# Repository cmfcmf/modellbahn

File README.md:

# Modellbahn

Eine Sammlung von Hardware und Software, die ich auf meiner Modelleisenbahnanlage verwende.

Eine Übersicht über alle Projekte ist hier zu finden: https://cmfcmf.github.io/modellbahn.

Lokal kann man die Website folgendermaßen bauen:

    bundle exec jekyll serve --livereload

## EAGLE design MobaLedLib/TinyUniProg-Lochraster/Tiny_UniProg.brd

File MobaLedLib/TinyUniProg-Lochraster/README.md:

---
layout: project
tags: [arduino, arduino nano, mobaledlib]
permalink: mobaledlib/tiny-uni-prog-lochraster-arduino-nano
state: finished
---

# Lochraster-Version der _TinyUniProg_-Platine für die MobaLedLib für Arduino Nano

Bei diesem Projekt handelt es sich um eine Lochraster-Variante der _TinyUniProg_-Platine der [MobaLedLib](https://github.com/Hardi-St/MobaLedLib_Docu).
Sie basiert auf dem [Original-Schaltplan](https://github.com/Hardi-St/MobaLedLib_Docu/blob/75f16147031ef20691729545cb87e0a1215a445a/Platinen/Tiny_UniProg.zip), allerdings ohne Debug-Hardware und auf Basis eines Arduino Nano statt Uno.

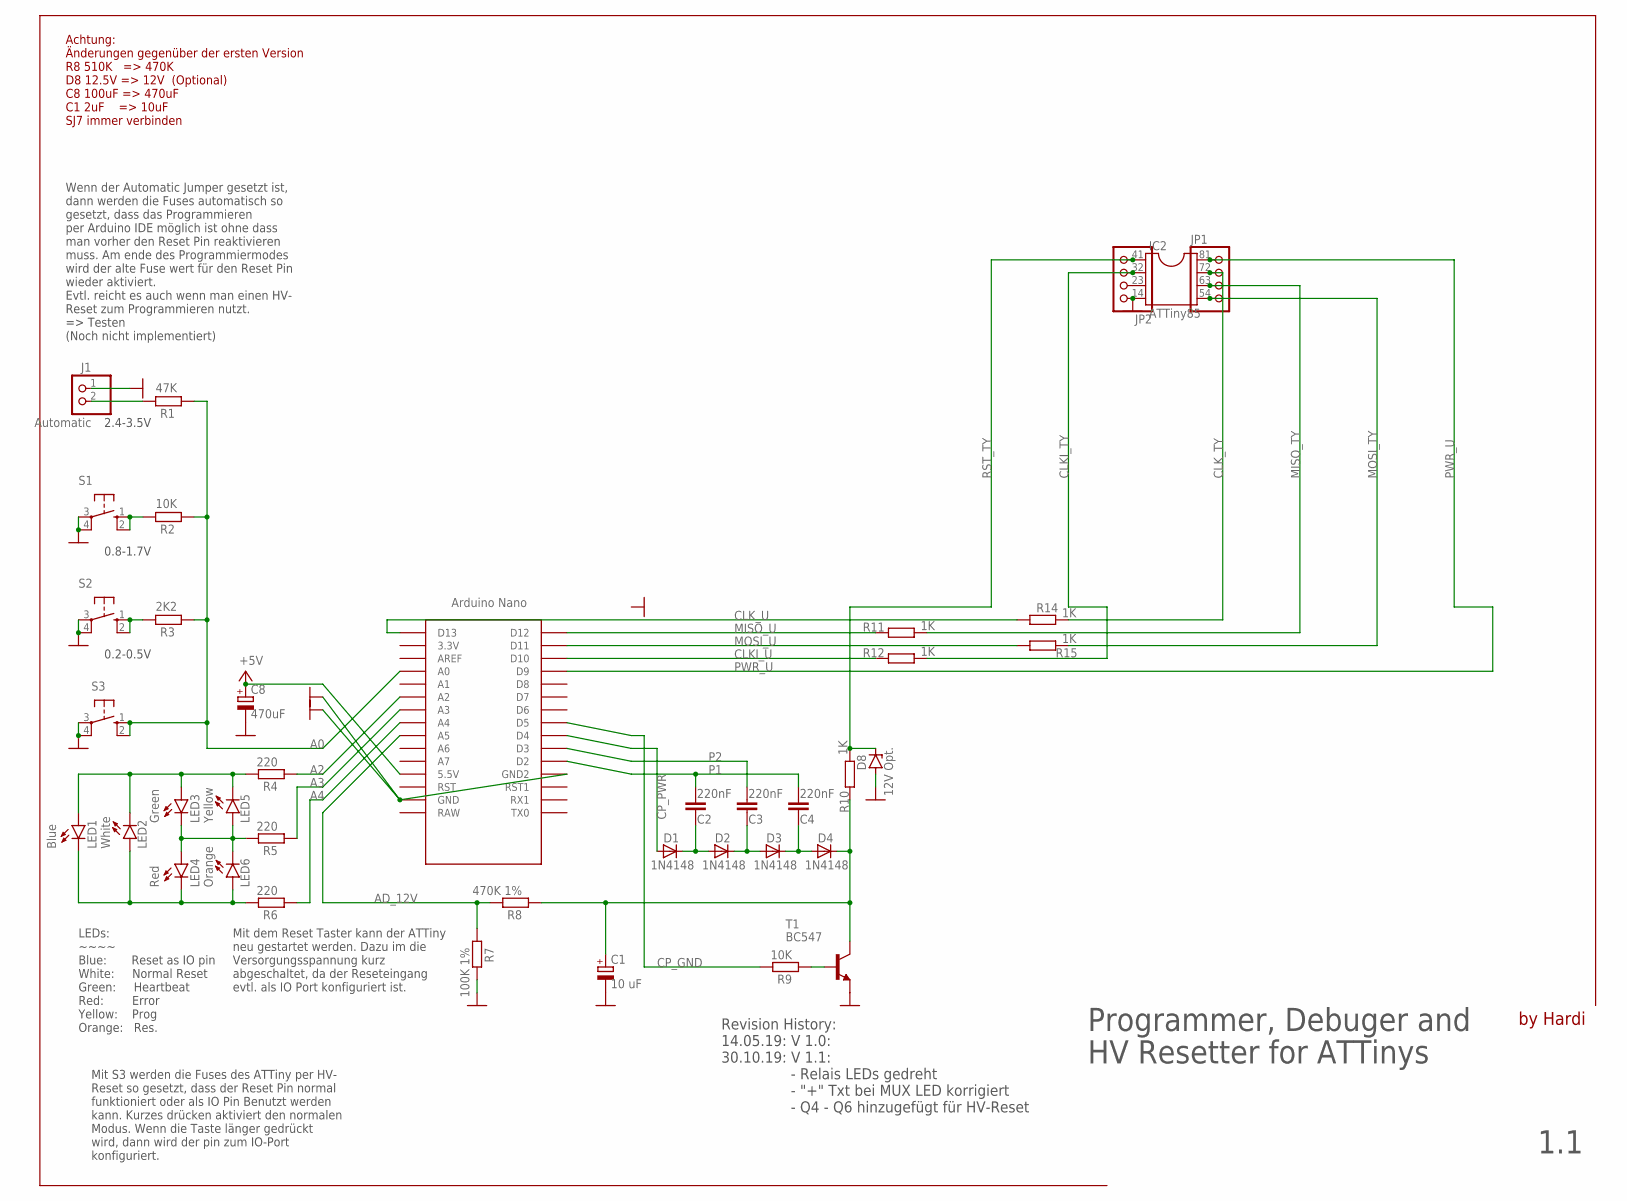
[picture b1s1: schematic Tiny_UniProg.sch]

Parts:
C1: 10 uF; E5-5
C2, C3, C4: 220nF; C050-024X044
C8: 470uF; E5-10,5
D1, D2, D3, D4: 1N4148; DO35-2
D8: 12V Opt.; ZDIO-2.5
IC2: ATTiny85; DIL08
J1: Automatic; 1X02
JP1, JP2: PINHD-1X4; 1X04
LED1: Blue; LED3MM
LED2: White; LED3MM
LED3: Green; LED3MM
LED4: Red; LED3MM
LED5: Yellow; LED3MM
LED6: Orange; LED3MM
R1: 47K; 0204V
R2: 10K; 0204V
R3: 2K2; 0204V
R4, R6: 220; 0204/5
R5: 220; 0204V
R7: 100K 1%; 0204/7
R8: 470K 1%; 0204V
R9: 10K; 0207/12
R10, R11: 1K; 0204V
R12, R15: 1K; 0204/5
R14: 1K; 0207/12
S1, S2, S3: 10-XX; B3F-10XX
T1: BC547; TO92
U$1: NANO

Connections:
+5V: C8.+, U$1.5V (5.5V)
A0: R1.1, R2.1, R3.1, S3.1 (S), S3.2 (S1), U$1.A0
A2: R4.1, U$1.A2
A3: R5.1, U$1.A3
A4: R6.1, U$1.A4
AD_12V: R7.1, R8.2, U$1.A5
CLKI_TY: IC2.2, JP2.3, R12.2
CLKI_U: R12.1, U$1.D10
CLK_TY: IC2.7, JP1.2, R14.2
CLK_U: R14.1, U$1.D13
CP_GND: R9.2, U$1.D5
CP_PWR: D1.A, U$1.D4
GND: C1.-, C8.-, D8.A, IC2.4, J1.1, JP2.1, R7.2, S1.3, S1.4 (P1), S2.3, S2.4 (P1), S3.3, S3.4 (P1), T1.1 (E), U$1.GND, U$1.GND1 (GND2)
MISO_TY: IC2.6, JP1.3, R11.2
MISO_U: R11.1, U$1.D12
MOSI_TY: IC2.5, JP1.4, R15.2
MOSI_U: R15.1, U$1.D11
unnamed: C2.2, D1.C, D2.A
unnamed: C3.2, D2.C, D3.A
unnamed: C4.2, D3.C, D4.A
unnamed: IC2.3, JP2.2
unnamed: R9.1, T1.2 (B)
unnamed: C1.+, D4.C, R8.1, R10.2, T1.3 (C)
unnamed: J1.2, R1.2
unnamed: R3.2, S2.1 (S), S2.2 (S1)
unnamed: LED1.A, LED2.K (C), LED3.A, LED5.K (C), R4.2
unnamed: LED3.K (C), LED4.A, LED5.A, LED6.K (C), R5.2
unnamed: LED1.K (C), LED2.A, LED4.K (C), LED6.A, R6.2
unnamed: R2.2, S1.1 (S), S1.2 (S1)
P1: C2.1, C4.1, U$1.D2
P2: C3.1, U$1.D3
PWR_U: IC2.8, JP1.1, U$1.D9
RST_TY: D8.C, IC2.1, JP2.4, R10.1

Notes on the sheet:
Mit S3 werden die Fuses des ATTiny per HV- Reset so gesetzt, dass der Reset Pin normal funktioniert oder als IO Pin Benutzt werden kann. Kurzes drücken aktiviert den normalen Modus. Wenn die Taste länger gedrückt wird, dann wird der pin zum IO-Port konfiguriert.
Mit dem Reset Taster kann der ATTiny neu gestartet werden. Dazu im die Versorgungsspannung kurz abgeschaltet, da der Reseteingang evtl. als IO Port konfiguriert ist.
Wenn der Automatic Jumper gesetzt ist, dann werden die Fuses automatisch so gesetzt, dass das Programmieren per Arduino IDE möglich ist ohne dass man vorher den Reset Pin reaktivieren muss. Am ende des Programmiermodes wird der alte Fuse wert für den Reset Pin wieder aktiviert. Evtl. reicht es auch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
LEDs: ~~~~ Blue: Reset as IO pin White: Normal Reset Green: Heartbeat Red: Error Yellow: Prog Orange: Res.
by Hardi
Programmer, Debuger and HV Resetter for ATTinys
0.2-0.5V
0.8-1.7V
2.4-3.5V
Achtung: Änderungen gegenüber der ersten Version R8 510K => 470K D8 12.5V => 12V (Optional) C8 100uF => 470uF C1 2uF => 10uF SJ7 immer verbinden
Revision History: 14.05.19: V 1.0: 30.10.19: V 1.1: - Relais LEDs gedreht - "+" Txt bei MUX LED korrigiert - Q4 - Q6 hinzugefügt für HV-Reset
1.1

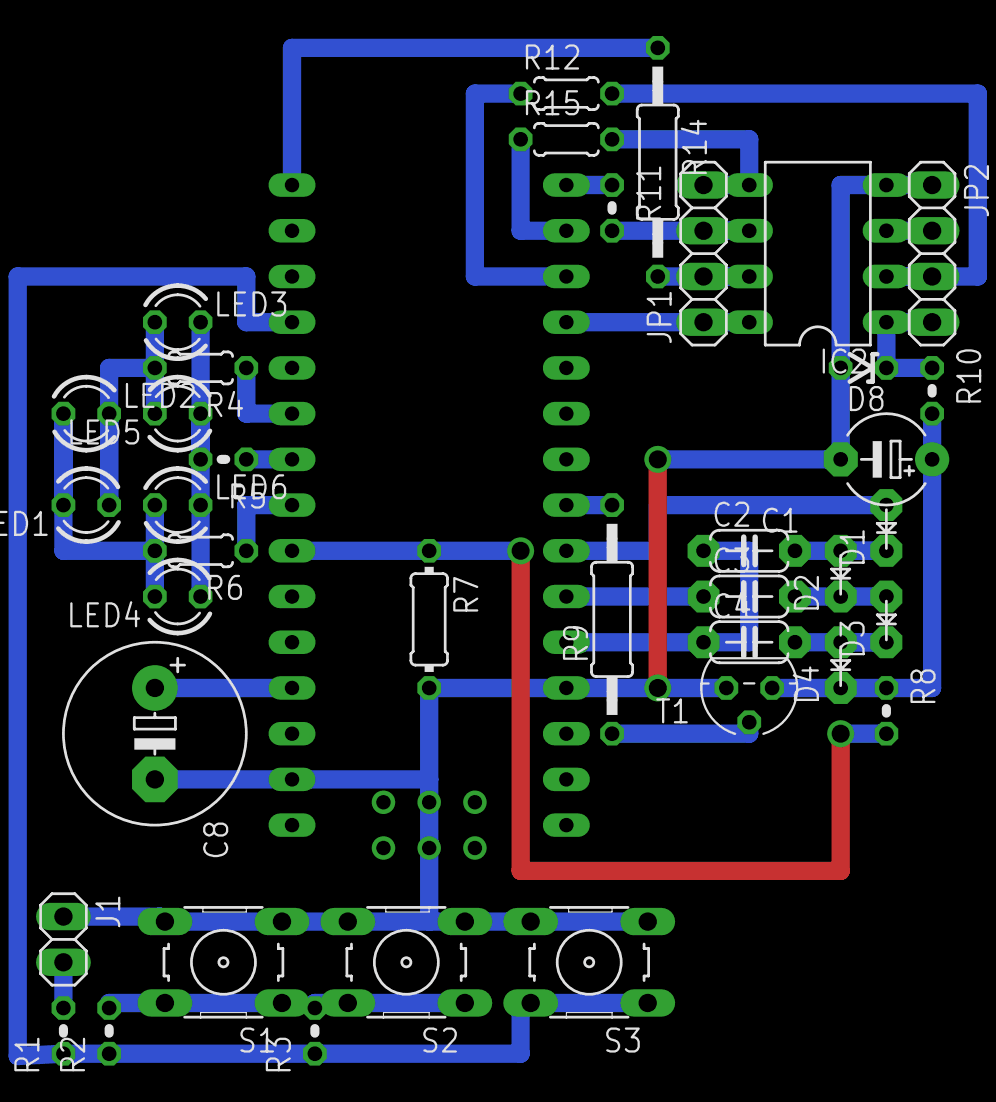
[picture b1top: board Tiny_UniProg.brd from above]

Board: 2 copper layers, 39 parts (0 on the bottom side), 33 nets.

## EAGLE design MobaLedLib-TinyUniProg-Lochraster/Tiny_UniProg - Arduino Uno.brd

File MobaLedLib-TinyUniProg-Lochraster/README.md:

---
layout: project
tags: [arduino, arduino nano, mobaledlib]
permalink: mobaledlib/tiny-uni-prog-lochraster-arduino-nano
state: finished
---

# Lochraster-Version der _TinyUniProg_-Platine für die MobaLedLib für Arduino Nano

Bei diesem Projekt handelt es sich um eine Lochraster-Variante der _TinyUniProg_-Platine der [MobaLedLib](https://github.com/Hardi-St/MobaLedLib_Docu).
Sie basiert auf dem [Original-Schaltplan](https://github.com/Hardi-St/MobaLedLib_Docu/blob/75f16147031ef20691729545cb87e0a1215a445a/Platinen/Tiny_UniProg.zip), allerdings ohne Debug-Hardware und auf Basis eines Arduino Nano statt Uno.

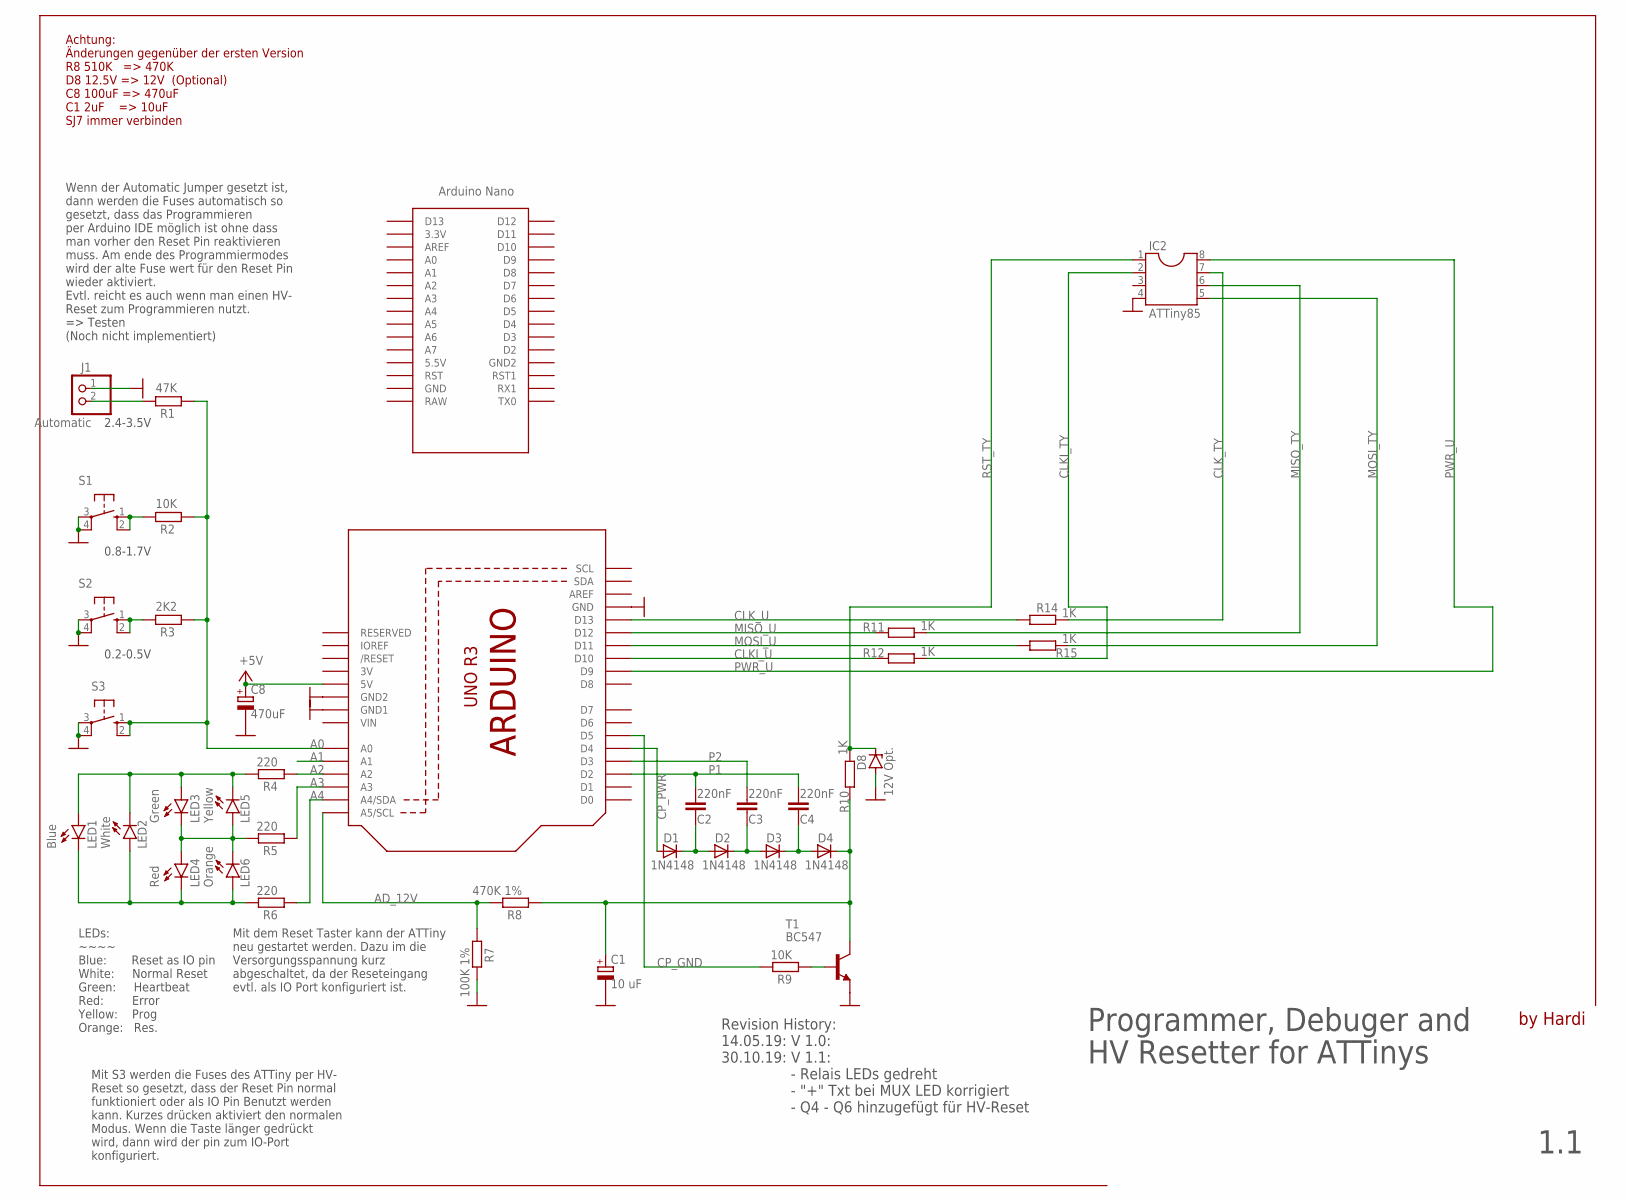
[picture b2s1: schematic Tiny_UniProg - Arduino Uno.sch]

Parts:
C1: 10 uF; E5-5
C2, C3, C4: 220nF; C050-024X044
C8: 470uF; E5-10,5
D1, D2, D3, D4: 1N4148; DO35-2
D8: 12V Opt.; ZDIO-2.5
IC2: ATTiny85; DIL08
J1: Automatic; 1X02
LED1: Blue; LED3MM
LED2: White; LED3MM
LED3: Green; LED3MM
LED4: Red; LED3MM
LED5: Yellow; LED3MM
LED6: Orange; LED3MM
R1: 47K; 0204/5
R2: 10K; 0204V
R3: 2K2; 0204V
R4, R6: 220; 0204/5
R5: 220; 0204V
R7: 100K 1%; 0204/7
R8: 470K 1%; 0204V
R9: 10K; 0204/7
R10: 1K; 0207/15
R11, R14, R15: 1K; 0204V
R12: 1K; 0207/7
S1, S2, S3: 10-XX; B3F-10XX
T1: BC547; TO92
U1: ARDUINOR3-DIMENSION; ARDUINOR3
U$1: NANO

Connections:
3V: U1.3V
+5V: C8.+, U1.5V
A0: R1.1, R2.1, R3.1, S3.1 (S), S3.2 (S1), U1.A0
A1: U1.A1
A2: R4.1, U1.A2
A3: R5.1, U1.A3
A4: R6.1, U1.A4 (A4/SDA)
AD_12V: R7.1, R8.2, U1.A5 (A5/SCL)
CLKI_TY: IC2.2, R12.2
CLKI_U: R12.1, U1.D10
CLK_TY: IC2.7, R14.2
CLK_U: R14.1, U1.D13
CP_GND: R9.2, U1.D5
CP_PWR: D1.A, U1.D4
GND: C1.-, C8.-, D8.A, IC2.4, J1.1, R7.2, S1.3, S1.4 (P1), S2.3, S2.4 (P1), S3.3, S3.4 (P1), T1.1 (E), U1.GND, U1.GND1, U1.GND2
MISO_TY: IC2.6, R11.2
MISO_U: R11.1, U1.D12
MOSI_TY: IC2.5, R15.2
MOSI_U: R15.1, U1.D11
unnamed: C2.2, D1.C, D2.A
unnamed: C3.2, D2.C, D3.A
unnamed: C4.2, D3.C, D4.A
unnamed: R9.1, T1.2 (B)
unnamed: C1.+, D4.C, R8.1, R10.2, T1.3 (C)
unnamed: J1.2, R1.2
unnamed: R3.2, S2.1 (S), S2.2 (S1)
unnamed: LED1.A, LED2.K (C), LED3.A, LED5.K (C), R4.2
unnamed: LED3.K (C), LED4.A, LED5.A, LED6.K (C), R5.2
unnamed: LED1.K (C), LED2.A, LED4.K (C), LED6.A, R6.2
unnamed: R2.2, S1.1 (S), S1.2 (S1)
P1: C2.1, C4.1, U1.D2
P2: C3.1, U1.D3
PWR_U: IC2.8, U1.D9
RST_TY: D8.C, IC2.1, R10.1
VIN: U1.VIN

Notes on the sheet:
Mit S3 werden die Fuses des ATTiny per HV- Reset so gesetzt, dass der Reset Pin normal funktioniert oder als IO Pin Benutzt werden kann. Kurzes drücken aktiviert den normalen Modus. Wenn die Taste länger gedrückt wird, dann wird der pin zum IO-Port konfiguriert.
Mit dem Reset Taster kann der ATTiny neu gestartet werden. Dazu im die Versorgungsspannung kurz abgeschaltet, da der Reseteingang evtl. als IO Port konfiguriert ist.
Wenn der Automatic Jumper gesetzt ist, dann werden die Fuses automatisch so gesetzt, dass das Programmieren per Arduino IDE möglich ist ohne dass man vorher den Reset Pin reaktivieren muss. Am ende des Programmiermodes wird der alte Fuse wert für den Reset Pin wieder aktiviert. Evtl. reicht es auch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
LEDs: ~~~~ Blue: Reset as IO pin White: Normal Reset Green: Heartbeat Red: Error Yellow: Prog Orange: Res.
by Hardi
Programmer, Debuger and HV Resetter for ATTinys
0.2-0.5V
0.8-1.7V
2.4-3.5V
Achtung: Änderungen gegenüber der ersten Version R8 510K => 470K D8 12.5V => 12V (Optional) C8 100uF => 470uF C1 2uF => 10uF SJ7 immer verbinden
Revision History: 14.05.19: V 1.0: 30.10.19: V 1.1: - Relais LEDs gedreht - "+" Txt bei MUX LED korrigiert - Q4 - Q6 hinzugefügt für HV-Reset
1.1

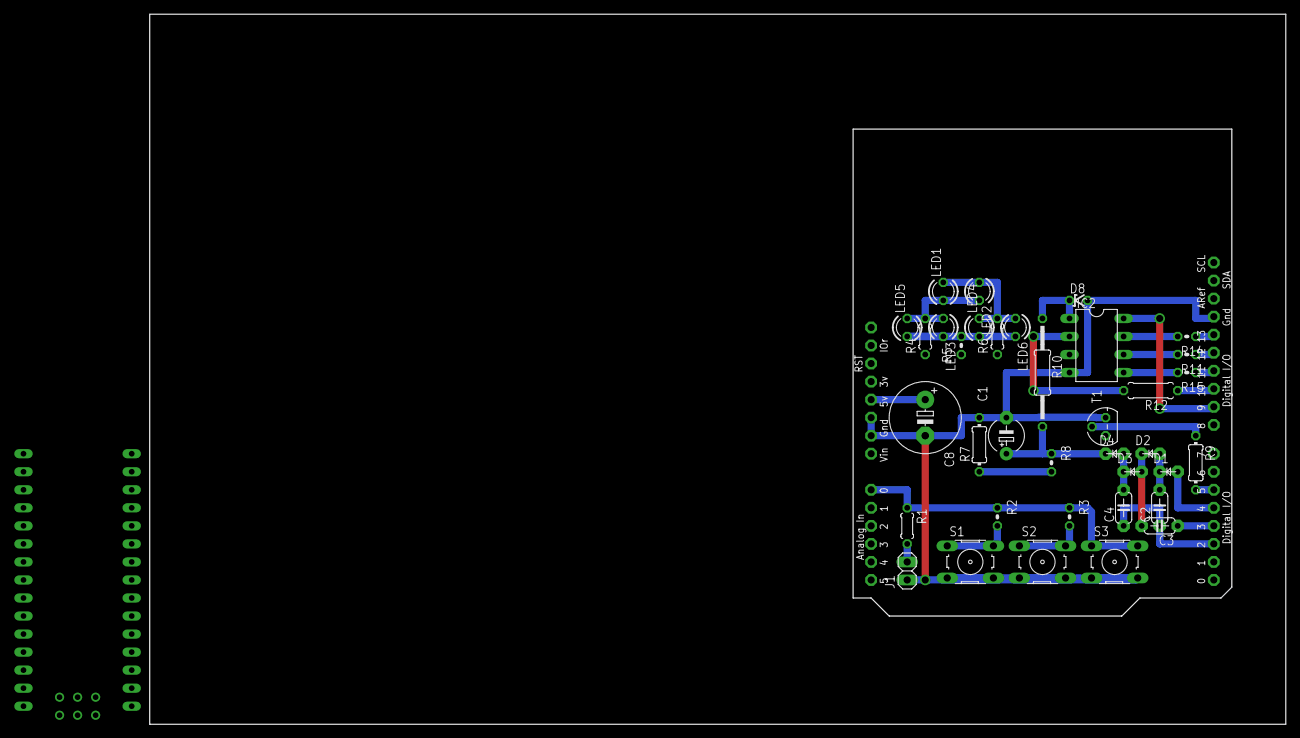
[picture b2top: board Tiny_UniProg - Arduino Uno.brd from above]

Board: 2 copper layers, 160.0 x 100.0 mm, 38 parts (0 on the bottom side), 32 nets.

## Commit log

2019-12-27 Initial commit.
2019-12-27 Add jekyll site
2019-12-27 Infos zur Wagenbeleuchtung
2019-12-27 Fix support for serving from subdirectory
2019-12-27 Use GitHub's STL viewer
2019-12-27 Add mathjax support
2019-12-27 Allgemeines zur Wagenbeleuchtung
2019-12-27 Sortiere Projekte nach Titel
2019-12-29 Minor site improvements
2019-12-29 Add section on multiplex signals
2019-12-29 Fix language, add sitemap
2019-12-29 Add support for project states
2019-12-30 Introduce "related projects"
2019-12-30 Fix typo
2019-12-30 Add privacy policy link
2019-12-30 Import MultiplexDecoder project
2019-12-30 Add code highlighting support
2019-12-30 Performance improvements, do not persist state in demo mode
2019-12-31 Make Serial and dark aspects optional, use watchdog as coarse timer
2019-12-31 Allow separate addresses per signal, improve address programming experience
2019-12-31 Show filename in code box footer
2020-01-01 Detect some file types from file content
2020-01-01 Improve documentation
2020-01-01 Adjust pin mapping for board layout
2020-01-01 Create schematic and pcb with KiCad
2020-01-01 Document hardware
2020-01-04 Split up dimming updates across multiple invocations of the ISR
    This makes it less likely that an INT0 edge may be missed
2020-01-04 Add makefile and proof of concept test using simulavr
2020-01-04 Fix signal aspect order to match what the CS2 expects
2020-01-04 Move templates into .h to be Arduino IDE-compatible
2020-01-05 Add information on dccpp
2020-01-05 Minor fixes
2020-02-06 Add state: finished to Schleppschalter Umbau
2020-02-26 Bump nokogiri from 1.10.7 to 1.10.8
    Bumps [nokogiri](https://github.com/sparklemotion/nokogiri) from 1.10.7 to 1.10.8.
    - [Release notes](https://github.com/sparklemotion/nokogiri/releases)
    - [Changelog](https://github.com/sparklemotion/nokogiri/blob/master/CHANGELOG.md)
    - [Commits](https://github.com/sparklemotion/nokogiri/compare/v1.10.7...v1.10.8)
2020-05-26 Bump activesupport from 6.0.2.1 to 6.0.3.1
    Bumps [activesupport](https://github.com/rails/rails) from 6.0.2.1 to 6.0.3.1.
    - [Release notes](https://github.com/rails/rails/releases)
    - [Changelog](https://github.com/rails/rails/blob/v6.0.3.1/activesupport/CHANGELOG.md)
    - [Commits](https://github.com/rails/rails/compare/v6.0.2.1...v6.0.3.1)
2020-07-29 Start working on an EP2C5T144 tutorial
2020-08-11 More tutorial steps
2021-02-02 Update dependencies
2021-02-02 Blue Pill Docs
2021-02-10 Fix formatting
2021-03-26 Add TinyUniProg pcb
2021-03-26 Fixes + images
2021-03-28 Create MobaLedLib subdirectory
2021-03-28 Add PDK bipolar signal driver
2021-03-28 Fix tags
2021-04-30 Bump rexml from 3.2.4 to 3.2.5
    Bumps [rexml](https://github.com/ruby/rexml) from 3.2.4 to 3.2.5.
    - [Release notes](https://github.com/ruby/rexml/releases)
    - [Changelog](https://github.com/ruby/rexml/blob/master/NEWS.md)
    - [Commits](https://github.com/ruby/rexml/compare/v3.2.4...v3.2.5)
2021-05-04 Fix image urls
2021-05-20 Bump nokogiri from 1.11.1 to 1.11.5
    Bumps [nokogiri](https://github.com/sparklemotion/nokogiri) from 1.11.1 to 1.11.5.
    - [Release notes](https://github.com/sparklemotion/nokogiri/releases)
    - [Changelog](https://github.com/sparklemotion/nokogiri/blob/main/CHANGELOG.md)
    - [Commits](https://github.com/sparklemotion/nokogiri/compare/v1.11.1...v1.11.5)
2021-07-13 Bump addressable from 2.7.0 to 2.8.0
    Bumps [addressable](https://github.com/sporkmonger/addressable) from 2.7.0 to 2.8.0.
    - [Release notes](https://github.com/sporkmonger/addressable/releases)
    - [Changelog](https://github.com/sporkmonger/addressable/blob/main/CHANGELOG.md)
    - [Commits](https://github.com/sporkmonger/addressable/compare/addressable-2.7.0...addressable-2.8.0)
    ---
    updated-dependencies:
2021-09-28 Bump nokogiri from 1.11.5 to 1.12.5
    Bumps [nokogiri](https://github.com/sparklemotion/nokogiri) from 1.11.5 to 1.12.5.
    - [Release notes](https://github.com/sparklemotion/nokogiri/releases)
    - [Changelog](https://github.com/sparklemotion/nokogiri/blob/main/CHANGELOG.md)
    - [Commits](https://github.com/sparklemotion/nokogiri/compare/v1.11.5...v1.12.5)
    ---
    updated-dependencies:
2022-02-26 Bump nokogiri from 1.12.5 to 1.13.3
    Bumps [nokogiri](https://github.com/sparklemotion/nokogiri) from 1.12.5 to 1.13.3.
    - [Release notes](https://github.com/sparklemotion/nokogiri/releases)
    - [Changelog](https://github.com/sparklemotion/nokogiri/blob/main/CHANGELOG.md)
    - [Commits](https://github.com/sparklemotion/nokogiri/compare/v1.12.5...v1.13.3)
    ---
    updated-dependencies:
2022-04-12 Bump nokogiri from 1.12.5 to 1.13.4
    Bumps [nokogiri](https://github.com/sparklemotion/nokogiri) from 1.12.5 to 1.13.4.
    - [Release notes](https://github.com/sparklemotion/nokogiri/releases)
    - [Changelog](https://github.com/sparklemotion/nokogiri/blob/v1.13.4/CHANGELOG.md)
    - [Commits](https://github.com/sparklemotion/nokogiri/compare/v1.12.5...v1.13.4)
    ---
    updated-dependencies:
2022-05-18 Bump nokogiri from 1.12.5 to 1.13.6
    Bumps [nokogiri](https://github.com/sparklemotion/nokogiri) from 1.12.5 to 1.13.6.
    - [Release notes](https://github.com/sparklemotion/nokogiri/releases)
    - [Changelog](https://github.com/sparklemotion/nokogiri/blob/main/CHANGELOG.md)
    - [Commits](https://github.com/sparklemotion/nokogiri/compare/v1.12.5...v1.13.6)
    ---
    updated-dependencies:
2022-07-22 Bump tzinfo from 1.2.9 to 1.2.10
    Bumps [tzinfo](https://github.com/tzinfo/tzinfo) from 1.2.9 to 1.2.10.
    - [Release notes](https://github.com/tzinfo/tzinfo/releases)
    - [Changelog](https://github.com/tzinfo/tzinfo/blob/master/CHANGES.md)
    - [Commits](https://github.com/tzinfo/tzinfo/compare/v1.2.9...v1.2.10)
    ---
    updated-dependencies:
2022-10-20 Bump nokogiri from 1.12.5 to 1.13.9
    Bumps [nokogiri](https://github.com/sparklemotion/nokogiri) from 1.12.5 to 1.13.9.
    - [Release notes](https://github.com/sparklemotion/nokogiri/releases)
    - [Changelog](https://github.com/sparklemotion/nokogiri/blob/main/CHANGELOG.md)
    - [Commits](https://github.com/sparklemotion/nokogiri/compare/v1.12.5...v1.13.9)
    ---
    updated-dependencies:
2023-01-31 Bump activesupport from 6.0.3.4 to 6.0.6.1
    Bumps [activesupport](https://github.com/rails/rails) from 6.0.3.4 to 6.0.6.1.
    - [Release notes](https://github.com/rails/rails/releases)
    - [Changelog](https://github.com/rails/rails/blob/v7.0.4.2/activesupport/CHANGELOG.md)
    - [Commits](https://github.com/rails/rails/compare/v6.0.3.4...v6.0.6.1)
    ---
    updated-dependencies:
2023-04-12 Bump nokogiri from 1.12.5 to 1.14.3
    Bumps [nokogiri](https://github.com/sparklemotion/nokogiri) from 1.12.5 to 1.14.3.
    - [Release notes](https://github.com/sparklemotion/nokogiri/releases)
    - [Changelog](https://github.com/sparklemotion/nokogiri/blob/main/CHANGELOG.md)
    - [Commits](https://github.com/sparklemotion/nokogiri/compare/v1.12.5...v1.14.3)
    ---
    updated-dependencies:
